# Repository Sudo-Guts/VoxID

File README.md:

# VoxID

Sistema embebido para identificar hablantes a partir de la palabra de referencia **MARIPOSA**.

La plataforma digital es **Ophyra con STM32F407VGT6**, pantalla ST7735 de 160 x 128 pixeles y cuatro pulsadores. El firmware principal esta en `C0DE/voxid`; los ocho modulos DSP estan dentro del mismo proyecto, en `C0DE/voxid/Core/Src` y `C0DE/voxid/Core/Inc`.

## Etapas y estado

| Etapa | Alcance | Estado |
|---|---|---|
| 1 | ADC1 + TIM2 + DMA y circulos de preparacion | Implementada; funcionamiento general reportado en Ophyra. Mediciones de temporizacion pendientes. |
| 2 | ADC a PCM y extraccion MFCC de audio real | Implementada y probada en PC; funcionamiento general reportado en Ophyra. Calibracion y mediciones pendientes. |
| 3 | Registro de tres prototipos MFCC por locutor | Implementada y probada en PC; funcionamiento general reportado en Ophyra. Ajustes con varias personas pendientes. |
| 4 | EEPROM M24C32 e identificacion por distancia normalizada | Implementada y probada en PC; funcionamiento general y navegacion de locutores confirmados por el usuario. Calibracion pendiente. |

La interfaz permite registrar cuatro locutores, con tres prototipos de 13 coeficientes por locutor. Los perfiles se guardan en EEPROM y se recuperan en RAM al arrancar. La identificacion compara una toma nueva con los tres prototipos de cada locutor y puede rechazar por distancia o ambiguedad. Los umbrales iniciales requieren calibracion; el codigo no verifica la palabra pronunciada.

## Adquisicion y procesamiento

La cadena prevista comprende microfono electret, preamplificacion, filtros pasaaltas y pasabajas, adaptacion de nivel al ADC y procesamiento digital.

| Parametro digital | Configuracion |
|---|---|
| Entrada | PA2, ADC1_IN2, 12 bits |
| Muestreo | 16 kHz, TIM2 TRGO; reloj TIM2 de 84 MHz, PSC 0 y ARR 5249 |
| Captura | 2500 ms, 40 000 muestras |
| DMA | DMA2 Stream0 Channel0, circular; dos mitades de 800 muestras |
| Tiempo entre mitades | 50 ms |
| Frame y avance | 400 muestras, 25 ms; avance de 160 muestras, 10 ms |
| Extraccion | Hamming, FFT de 512, potencia, 26 filtros Mel, logaritmo y DCT-II |
| Resultado | 248 vectores de 13 coeficientes por toma |

`voxid_config.h` concentra los parametros compartidos. La ISR notifica bloques; el bucle principal convierte ADC a PCM, elimina DC y procesa MFCC. Se usan buffers estaticos y no se guarda el audio completo.

La fase 2 de reorganizacion integra el adaptador MFCC en `voxid_voice.c` y declara sus funciones existentes en `voxid_voice.h`. Se retiran los dos archivos separados `voxid_dsp.c` y `voxid_dsp.h` del firmware principal, conservando las APIs y el procesamiento de tomas de 2.5 segundos.

La media MFCC utiliza unicamente frames cuya energia supera `VOXID_VOICE_MIN_RMS`. El umbral inicial es RMS 0.01 respecto de la escala completa y necesita calibracion con voz y ruido medidos en la placa. Un ruido suficientemente intenso tambien puede superar este criterio. Si no se selecciona ningun frame, la captura puede ser valida, pero la UI muestra `CON VOZ: 0` y no dibuja una media de voz.

## Registro de locutores

REGISTRAR permite elegir un locutor y capturar tres tomas independientes. OK acepta cada toma valida y empieza la siguiente; en la tercera confirma el guardado verificado en EEPROM. BACK descarta el registro pendiente y conserva el perfil anterior si existia.

El minimo inicial es de 20 frames seleccionados por toma, configurable en `voxid_config.h` y pendiente de calibracion fisica. Una toma insuficiente o un error se repite sin avanzar. Consultar [el flujo de etapa 3](DOC/STAGE3_ENROLLMENT.md) y [la persistencia e identificacion de etapa 4](DOC/STAGE4_STORAGE_IDENTIFY.md).

## Consulta de locutores

El menu ofrece IDENTIFICAR, REGISTRAR y LOCUTORES. En LOCUTORES, UP/DN selecciona uno de los cuatro espacios; se muestra su estado, cantidad de tomas y 13 MFCC por toma. OK abre las tomas de un perfil registrado. Dentro, UP/DN recorre TOMA 1/3, 2/3 y 3/3; BACK regresa al mismo locutor y otro BACK al menu. Los botones sin accion quedan sin texto y con el fondo inactivo de la paleta.

El estado de lectura o guardado pertenece a cada locutor: un error de otro espacio no modifica el mostrado para el seleccionado. Un registro no utilizable se muestra como `PERFIL NO UTILIZABLE` y pide `REGISTRA TRES TOMAS`.

Cada toma tiene su propia grafica C01..C12, normalizada a norma L2 unitaria y con escala fija -1..1; C00 queda fuera de la comparacion. El identificador promedia las tres distancias, por lo que se conservan las tres referencias. La consulta usa RAM, sin capturar audio, reiniciar el DSP ni escribir EEPROM. La EEPROM acepta unicamente perfiles de 248 frames y revision DSP 2. Todos los perfiles de revision 1, incluidos los de 2.5 segundos, deben registrarse de nuevo. La revision 2 fija los extremos del banco Mel a las frecuencias solicitadas; ver [la validacion numerica](DOC/STAGE2_REAL_MFCC.md).

## Identificacion y EEPROM

I2C1 utiliza PB6/PB7 a 100 kHz para la M24C32 integrada. Cada locutor dispone de dos copias con version y CRC: el reemplazo conserva la copia vigente hasta verificar la nueva. El arranque lee los perfiles sin formatear ni escribir. Un fallo de guardado permite reintentar la tercera toma sin volver a capturarla.

La distancia es el promedio de las tres distancias euclidianas entre vectores C01..C12 normalizados a norma L2 unitaria. Los valores iniciales son distancia maxima 0.35 y margen minimo 0.05 respecto al segundo candidato. La pantalla muestra LOCUTOR nn, DESCONOCIDO, VOZ AMBIGUA, SIN LOCUTORES o VOZ INSUFICIENTE. UP/DN conserva el acceso a la grafica MFCC y a las estadisticas ADC.

Los parametros y la revision DSP estan en `voxid_config.h`; el [formato y las comprobaciones](DOC/STAGE4_STORAGE_IDENTIFY.md) describen sus limites y la calibracion pendiente.

## Organizacion

| Ruta | Responsabilidad |
|---|---|
| `C0DE/voxid` | Unico proyecto de firmware para STM32CubeIDE. |
| `C0DE/voxid/Core/Inc`, `C0DE/voxid/Core/Src` | Firmware y ocho modulos DSP integrados. |
| `C0DE/voxid/Drivers` | HAL y CMSIS del fabricante. |
| `DOC` | Seguimiento y validacion. |
| `PCB` | Proyecto KiCad `voxid` y archivos de fabricacion versionados. |
| `SIM` | Preparacion de grabaciones en MATLAB, antecedentes PSIM y experimentos SPICE; ver [la guia](SIM/README.md). |

## Compilar el firmware

1. Importar directamente `C0DE/voxid` en STM32CubeIDE: los ocho modulos DSP son archivos fisicos de `Core`, sin enlaces externos.
2. Confirmar que `Core/Src` contenga frame, window, fft, power, mel, log_mel, dct y mfcc, ademas de los modulos del firmware.
3. Refrescar con F5, ejecutar Clean y Build Debug, y programar Ophyra.
4. Seguir [la validacion de etapas 1 y 2](DOC/Validacion_etapas_1_2.md), [el registro de etapa 3](DOC/STAGE3_ENROLLMENT.md) y [la validacion de etapa 4](DOC/STAGE4_STORAGE_IDENTIFY.md).

Dentro de `C0DE` queda unicamente `voxid`, con las fuentes del firmware y los archivos de STM32CubeIDE. Las guias se concentran en `DOC`. El proyecto de firmware no incluye ejecutables de PC, pruebas, sustitutos HAL ni un Makefile de PC.

Los modulos propios de Core siguen `Estandar_Programacion.md` v2.0: ASCII, cabeceras consistentes, rutas correctas y argumentos de funciones en una linea. Se conservan las APIs y algoritmos; los archivos autogenerados y HAL/CMSIS mantienen su formato original.

Si CubeMX regenera codigo, comprobar la configuracion DMA del `.ioc`, la vinculacion con ADC1 y el orden GPIO, DMA, ADC1, SPI1, TIM2, I2C1 y los GPIO PB6/PB7 de I2C1.

## Hardware y simulaciones

`main` integra el firmware de las cuatro etapas, el diseno analogico de `PCB/voxid.kicad_sch` y `PCB/voxid.kicad_pcb`, sus archivos de fabricacion y el trabajo de simulacion. Se conserva `pcb-sim` para continuar los cambios de hardware y simulacion; las ramas de etapas incorporadas se retiran sin borrar sus commits.

Los tres experimentos SPICE actualizados usan los dieciseis componentes comerciales de las cuatro secciones de filtro de la PCB. Desde la raiz, comprobar su correspondencia con:

```bash
python3 SIM/tests/comprobar_valores.py
```

Los antecedentes PSIM y los resultados historicos de filtros se conservan por separado en `SIM`. Deben repetirse los analisis AC, Monte Carlo y ruido con los valores vigentes. Las simulaciones, los Gerbers y los archivos KiCad no acreditan por si solos mediciones fisicas ni aprobacion ERC/DRC o de fabricacion.

La preparacion de grabaciones en MATLAB lee archivos o una carpeta, selecciona un canal, retira la media y remuestrea a 16 kHz cuando hace falta. Exporta WAV, CSV y MAT sin modificar los originales. Sus grabaciones y resultados locales quedan fuera de Git. Esta preparacion todavia no calcula MFCC ni identifica locutores; la ejecucion de sus pruebas en MATLAB y la lectura de un MP4 real siguen pendientes. Consultar [SIM/README.md](SIM/README.md) para requisitos y comandos.

El usuario reporto reconocimiento funcional con tomas de tres segundos y fallos al usar 2.5 segundos. La configuracion actual mantiene 16 kHz, 40 000 muestras y 248 frames; el algoritmo de comparacion y sus umbrales no se cambian sin mediciones. Falta comprobar en Ophyra la causa de los fallos, la temporizacion y la calibracion. Consultar [el seguimiento](DOC/CheckList.txt).

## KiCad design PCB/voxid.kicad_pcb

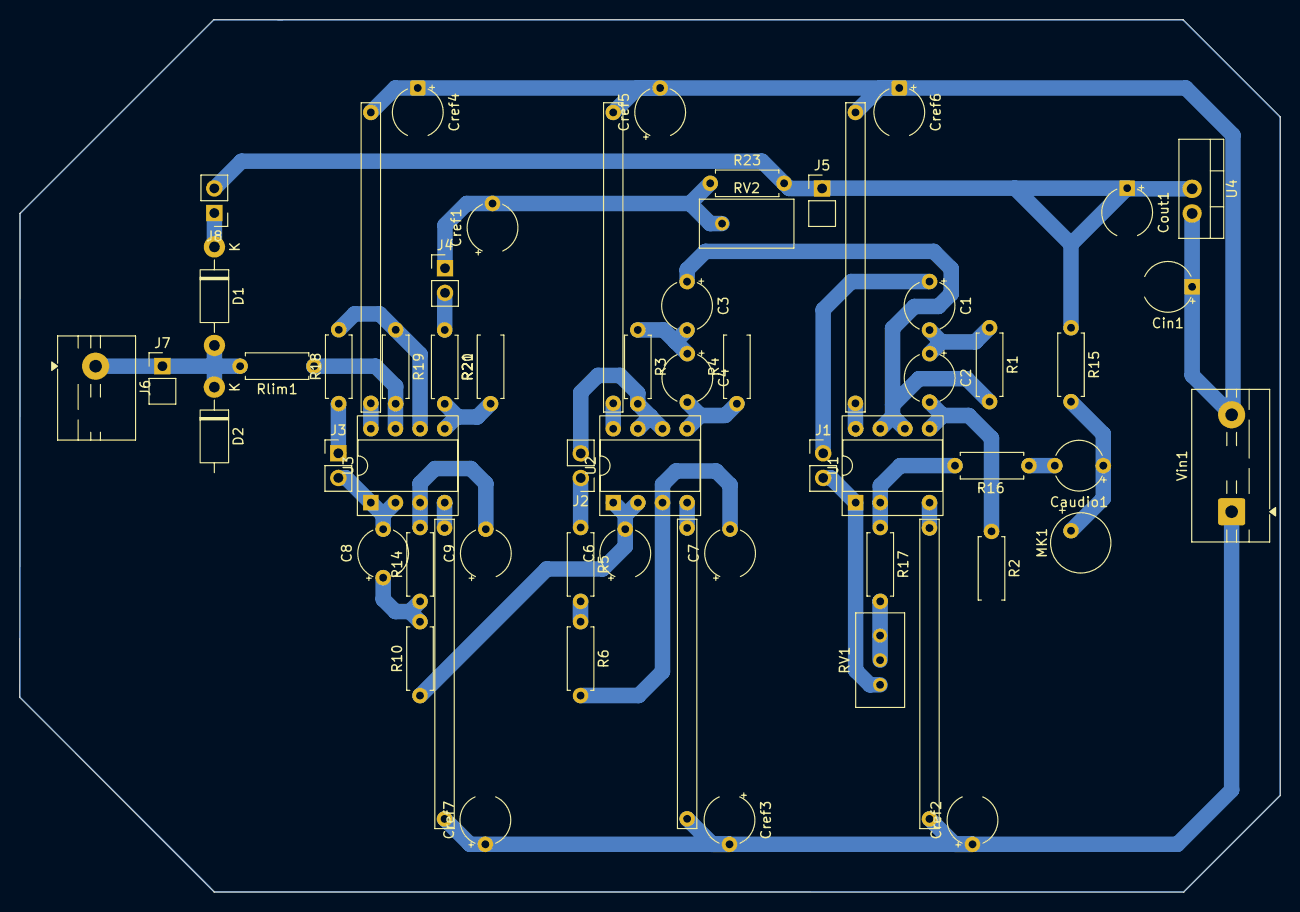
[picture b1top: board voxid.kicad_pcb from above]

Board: 2 copper layers, 130.0 x 90.0 mm, 59 parts (0 on the bottom side), 30 nets.

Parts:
C1, C2, C3, C4: 470nF; CP_Radial_Tantal_D5.0mm_P5.00mm
C6, C8: 22nF; CP_Radial_Tantal_D5.0mm_P5.00mm
C7: 2.2nF; CP_Radial_Tantal_D5.0mm_P5.00mm
C9: 10nF; CP_Radial_Tantal_D5.0mm_P5.00mm
Caudio1: 1uF; CP_Radial_Tantal_D5.0mm_P5.00mm
Cin1: 100nF; CP_Radial_Tantal_D5.0mm_P5.00mm
Cout1: 10uF; CP_Radial_Tantal_D5.0mm_P5.00mm
Cref1: 22uF; CP_Radial_Tantal_D5.0mm_P5.00mm
Cref2, Cref3, Cref4, Cref5, Cref6, Cref7: 100nF; CP_Radial_Tantal_D5.0mm_P5.00mm
D1, D2: 1N5819; D_DO-41_SOD81_P10.16mm_Horizontal
J1: Audio; PinHeader_1x02_P2.54mm_Vertical
J2: HPF_O; PinHeader_1x02_P2.54mm_Vertical
J3: LPFO; PinHeader_1x02_P2.54mm_Vertical
J4, J8: Offset; PinHeader_1x02_P2.54mm_Vertical
J5, J7: v3.3; PinHeader_1x02_P2.54mm_Vertical
J6: AudioOut; TerminalBlock_MaiXu_MX126-5.0-02P_1x02_P5.00mm
MK1: Microphone; POM-2244P-C3310-2-R
R1: 1.2k; R_Axial_DIN0207_L6.3mm_D2.5mm_P7.62mm_Horizontal
R2: 8.2k; R_Axial_DIN0207_L6.3mm_D2.5mm_P7.62mm_Horizontal
R3: 3.3k; R_Axial_DIN0207_L6.3mm_D2.5mm_P7.62mm_Horizontal
R4, R14: 3.9k; R_Axial_DIN0207_L6.3mm_D2.5mm_P7.62mm_Horizontal
R5, R15: 2.2k; R_Axial_DIN0207_L6.3mm_D2.5mm_P7.62mm_Horizontal
R6: 6.8k; R_Axial_DIN0207_L6.3mm_D2.5mm_P7.62mm_Horizontal
R10: 820; R_Axial_DIN0207_L6.3mm_D2.5mm_P7.62mm_Horizontal
R16, R23: 1k; R_Axial_DIN0207_L6.3mm_D2.5mm_P7.62mm_Horizontal
R17, R18, R19, R20, R21: 10k; R_Axial_DIN0207_L6.3mm_D2.5mm_P7.62mm_Horizontal
RV1: 100k; Potentiometer_Bourns_3296W_Vertical
RV2: 1.05k; Potentiometer_Bourns_3296W_Vertical
Rlim1: 4.7k; R_Axial_DIN0207_L6.3mm_D2.5mm_P7.62mm_Horizontal
TP1, TP2, TP3, TP4, TP5, TP6: TestPoint; TestPoint_Bridge_Pitch7.62mm_Drill1.3mm
U1, U2, U3: TL072; DIP-8_W7.62mm_Socket
U4: LM1117T-3.3; TO-220-3_Vertical
Vin1: Conn_01x03; TerminalBlock_MaiXu_MX126-5.0-03P_1x03_P5.00mm

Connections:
+3.3V: Cout1.1, J5.1 (Pin_1_1), J8.2, R15.1, R23.2, U4.2 (VO)
+12V: Cin1.1, Cref4.1, Cref5.2, Cref6.1, TP1.1 (1_1), TP2.1 (1_1), TP3.1 (1_1), U1.8 (V+), U2.8 (V+), U3.8 (V+), U4.3 (VI), Vin1.3
-12V: Cref2.1, Cref3.2, Cref7.1, TP4.1 (1_1), TP5.1 (1_1), TP6.1 (1_1), U1.4 (V-), U2.4 (V-), U3.4 (V-), Vin1.1
HPF: J2.1, R5.1
LPF: J3.1, R18.1
unnamed: C1.2, C2.1, R1.1
unnamed: C3.2, C4.1, R3.1
unnamed: R5.2, R6.1
unnamed: C8.1, R10.2, R14.1
unnamed: Caudio1.2, R16.1
unnamed: D1.2 (A), D2.1 (K_1), J6.1 (Pin_1_1), J7.1 (Pin_1_1), Rlim1.2
unnamed: D1.1 (K), J8.1
unnamed: J1.2, RV1.3, U1.1
unnamed: J2.2, R3.2, U2.6 (-), U2.7
unnamed: C8.2, J3.2, U3.1, U3.2 (-)
unnamed: J4.2, R20.1
unnamed: Caudio1.1, MK1.2 (+_2), R15.2
unnamed: R17.2, RV1.1, RV1.2
unnamed: R16.2, R17.1, U1.2 (-)
unnamed: C2.2, R2.1, U1.5 (+)
unnamed: C3.1, R1.2, U1.6 (-), U1.7
unnamed: C7.2, R6.2, U2.3 (+)
unnamed: C6.2, R10.1, U2.1, U2.2 (-)
unnamed: C4.2, R4.1, U2.5 (+)
unnamed: C9.2, R14.2, U3.3 (+)
unnamed: R20.2, R21.1, U3.5 (+)
unnamed: R18.2, R19.1, U3.6 (-)
S: R19.2, Rlim1.1, U3.7
Sound: C1.1, J1.1
Vref: Cref1.2, J4.1, R23.1, RV2.3 (3_3)

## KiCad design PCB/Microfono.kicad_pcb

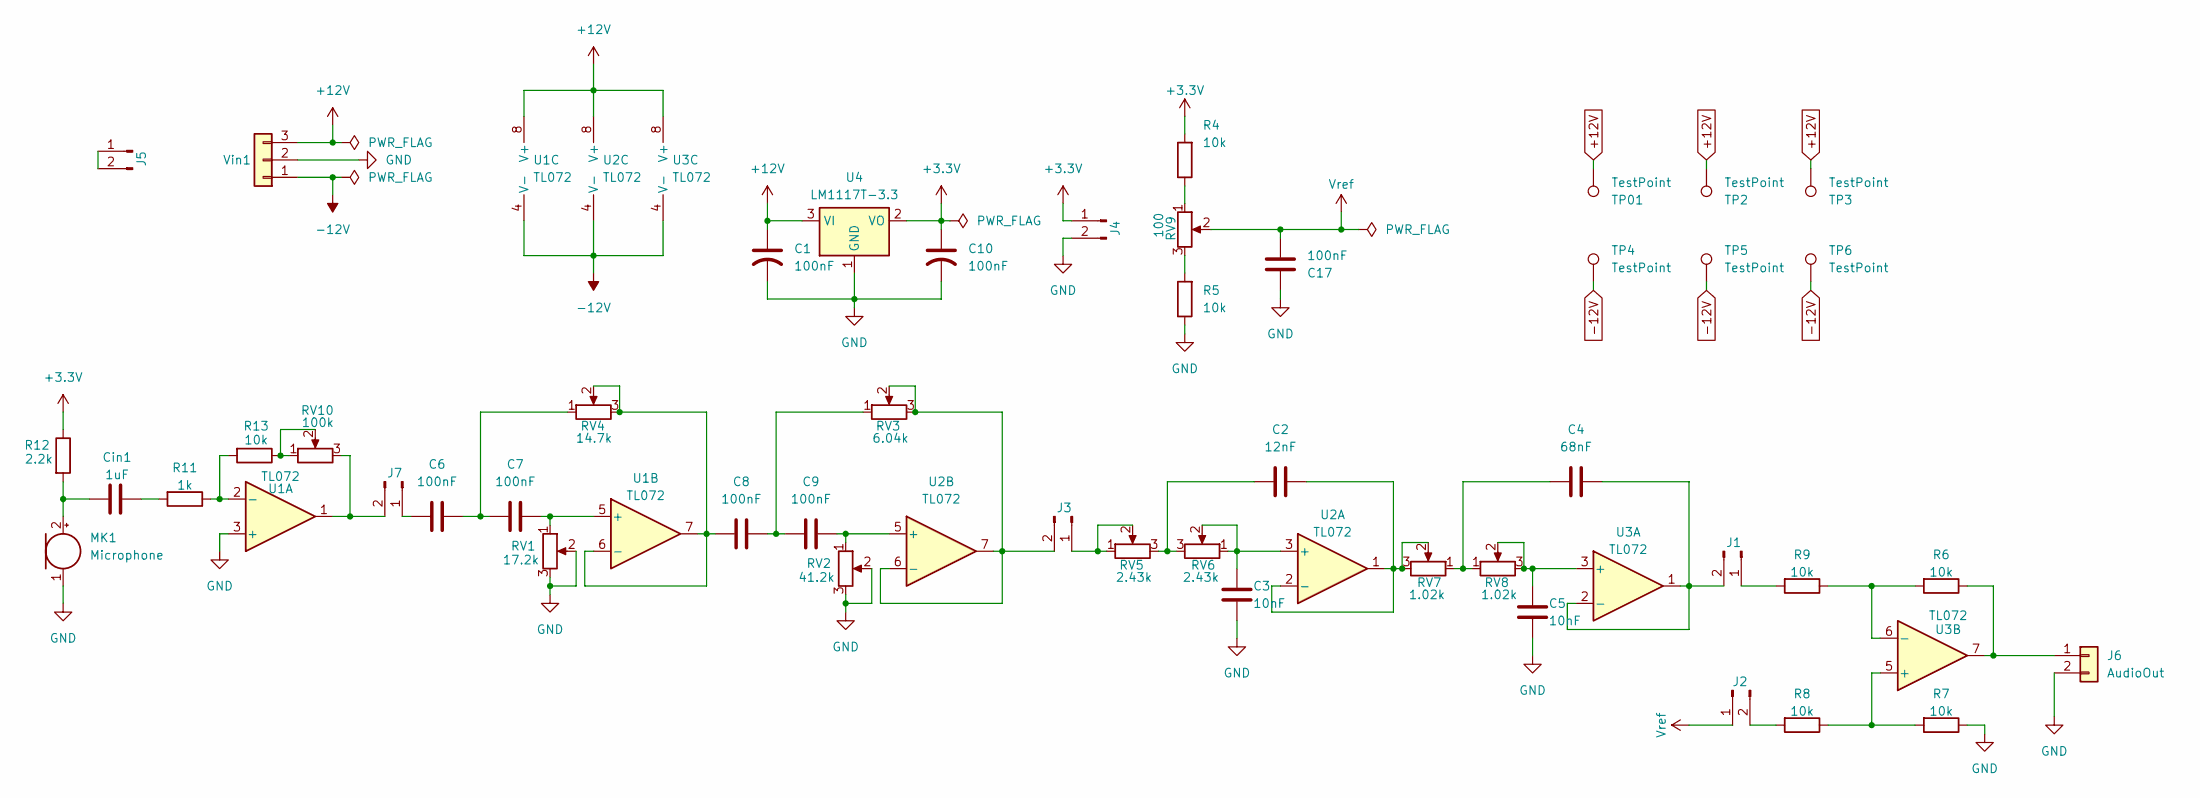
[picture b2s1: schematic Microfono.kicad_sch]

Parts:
C1, C6, C7, C8, C9, C10, C17: 100nF; CP_Radial_Tantal_D5.0mm_P5.00mm
C2: 12nF; CP_Radial_Tantal_D5.0mm_P5.00mm
C3, C5: 10nF; CP_Radial_Tantal_D5.0mm_P5.00mm
C4: 68nF; CP_Radial_Tantal_D5.0mm_P5.00mm
Cin1: 1uF; CP_Radial_Tantal_D5.0mm_P5.00mm
J1, J2, J3, J7: Conn_01x02_Pin; PinHeader_1x02_P2.54mm_Vertical
J4, J5: v3.3; PinHeader_1x02_P2.54mm_Vertical
J6: AudioOut; TerminalBlock_MaiXu_MX126-5.0-02P_1x02_P5.00mm
MK1: Microphone; POM-2244P-C3310-2-R
R4, R5, R6, R7, R8, R9, R13: 10k; R_Axial_DIN0309_L9.0mm_D3.2mm_P12.70mm_Horizontal
R11: 1k; R_Axial_DIN0309_L9.0mm_D3.2mm_P12.70mm_Horizontal
R12: 2.2k; R_Axial_DIN0309_L9.0mm_D3.2mm_P12.70mm_Horizontal
RV1: 17.2k; Potentiometer_Bourns_3296W_Vertical
RV2: 41.2k; Potentiometer_Bourns_3296W_Vertical
RV3: 6.04k; Potentiometer_Bourns_3296W_Vertical
RV4: 14.7k; Potentiometer_Bourns_3296W_Vertical
RV5, RV6: 2.43k; Potentiometer_Bourns_3296W_Vertical
RV7, RV8: 1.02k; Potentiometer_Bourns_3296W_Vertical
RV9: 100; Potentiometer_Bourns_3296W_Vertical
RV10: 100k; Potentiometer_Bourns_3296W_Vertical
TP01, TP2, TP3, TP4, TP5, TP6: TestPoint; TestPoint_Bridge_Pitch7.62mm_Drill1.3mm
U1, U2, U3: TL072; DIP-8_W7.62mm_Socket
U4: LM1117T-3.3; TO-220-3_Vertical
Vin1: Conn_01x03; TerminalBlock_MaiXu_MX126-5.0-03P_1x03_P5.00mm

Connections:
+3.3V: C10.1, J4.1 (Pin_1_1), R4.2, R12.1, U4.2 (VO)
+12V: C1.1, TP01.1 (1_1), TP2.1 (1_1), TP3.1 (1_1), U1.8 (V+), U2.8 (V+), U3.8 (V+), U4.3 (VI), Vin1.3
-12V: TP4.1 (1_1), TP5.1 (1_1), TP6.1 (1_1), U1.4 (V-), U2.4 (V-), U3.4 (V-), Vin1.1
unnamed: C2.1, RV5.3, RV6.3
unnamed: C4.1, RV7.1, RV8.1
unnamed: C6.2, C7.1, RV4.1
unnamed: C8.2, C9.1, RV3.1
unnamed: Cin1.2, R11.2
unnamed: J1.1, R9.2
unnamed: C4.2, J1.2, U3.1, U3.2 (-)
unnamed: J2.2, R8.2
unnamed: J3.1, RV5.1, RV5.2
unnamed: J3.2, RV3.2, RV3.3, U2.6 (-), U2.7
unnamed: J5.1, J5.2
unnamed: J6.1 (Pin_1_1), R6.1, U3.7
unnamed: C6.1, J7.1
unnamed: J7.2, RV10.3, U1.1
unnamed: Cin1.1, MK1.2 (+_2), R12.2
unnamed: R4.1, RV9.1
unnamed: R5.2, RV9.3
unnamed: R13.1, RV10.1, RV10.2
unnamed: R11.1, R13.2, U1.2 (-)
unnamed: C7.2, RV1.1 (1_1), U1.5 (+)
unnamed: C8.1, RV4.2, RV4.3, U1.6 (-), U1.7
unnamed: C3.1, RV6.1, RV6.2, U2.3 (+)
unnamed: C2.2, RV7.2, RV7.3, U2.1, U2.2 (-)
unnamed: C9.2, RV2.1 (1_1), U2.5 (+)
unnamed: C5.1, RV8.2, RV8.3, U3.3 (+)
unnamed: R7.2, R8.1, U3.5 (+)
unnamed: R6.2, R9.1, U3.6 (-)
Vref: C17.1, J2.1, RV9.2

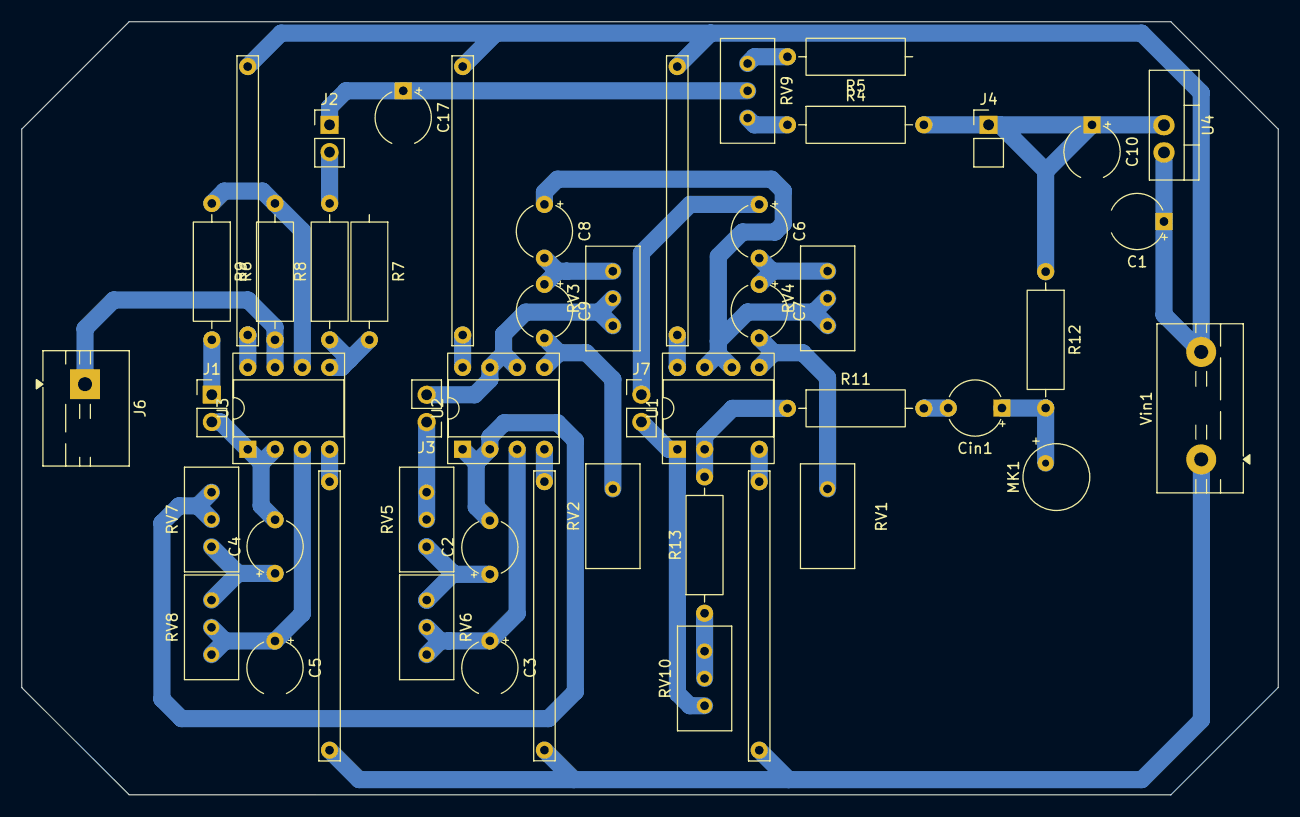
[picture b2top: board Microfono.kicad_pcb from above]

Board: 2 copper layers, 117.0 x 72.0 mm, 49 parts (0 on the bottom side), 30 nets.
